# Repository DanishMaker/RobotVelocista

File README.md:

# RobotVelocista
Un robot que corre ya esta joder

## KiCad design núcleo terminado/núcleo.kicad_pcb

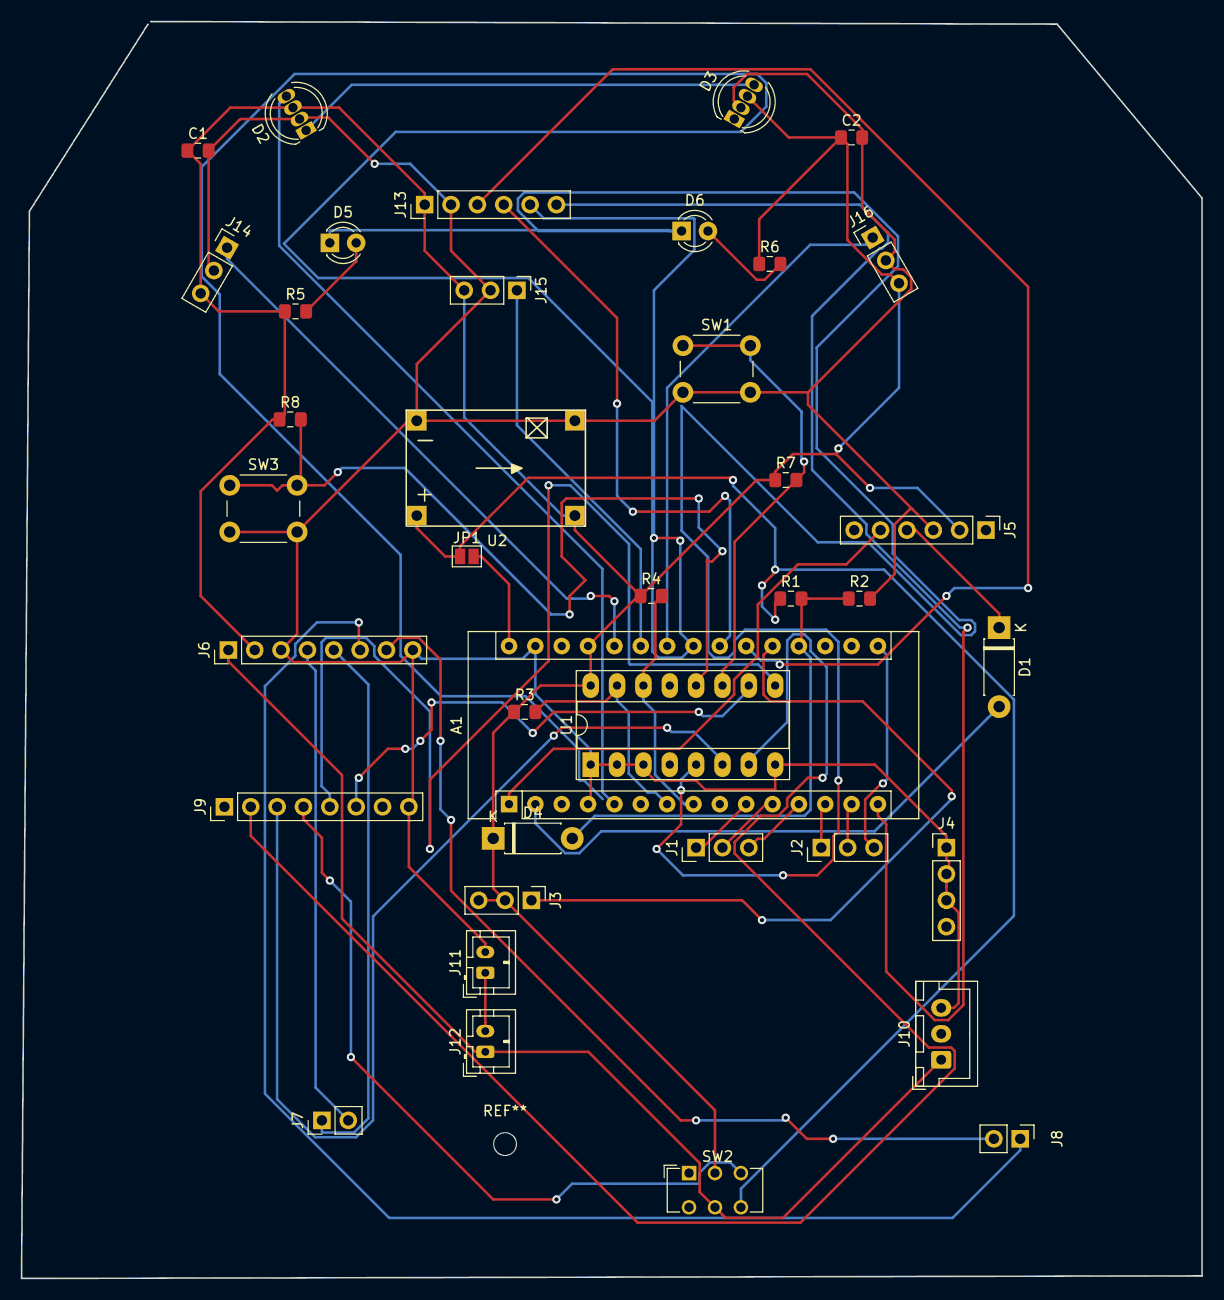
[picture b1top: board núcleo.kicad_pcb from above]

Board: 2 copper layers, 113.8 x 121.2 mm, 39 parts (0 on the bottom side), 42 nets.

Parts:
A1: Arduino_Nano_v3.x; Arduino_Nano
C1, C2: 100nF; C_0805_2012Metric_Pad1.15x1.40mm_HandSolder
D1, D4: D; D_DO-41_SOD81_P7.62mm_Horizontal
D2, D3: NeoPixel_THT; LED_D5.0mm-4_RGB
D5: LED_rojo; LED_D3.0mm
D6: LED_verde; LED_D3.0mm
J1: AUX1; PinHeader_1x03_P2.54mm_Vertical
J2: AUX2; PinHeader_1x03_P2.54mm_Vertical
J3: AUX3; PinHeader_1x03_P2.54mm_Vertical
J4: AUX4; PinHeader_1x04_P2.54mm_Vertical
J5: Conn_01x06; PinHeader_1x06_P2.54mm_Vertical
J6, J9: Conn_01x08; PinHeader_1x08_P2.54mm_Vertical
J7: MOT_IZQ; PinHeader_1x02_P2.54mm_Vertical
J8: MOT_DER; PinHeader_1x02_P2.54mm_Vertical
J10: Conn_01x03; JST_XH_B03B-XH-A_1x03_P2.50mm_Vertical
J11, J12: Conn_01x02; JST_PH_B2B-PH-K_1x02_P2.00mm_Vertical
J13: Sensores_linea; PinHeader_1x06_P2.54mm_Vertical
J14: DIST_IZQ; PinHeader_1x03_P2.54mm_Vertical
J15: DIST_FRONT; PinHeader_1x03_P2.54mm_Vertical
J16: DIST_DCHA; PinHeader_1x03_P2.54mm_Vertical
JP1: Jumper_NO_Small; SolderJumper-2_P1.3mm_Open_Pad1.0x1.5mm
R1: 82k; R_0805_2012Metric_Pad1.15x1.40mm_HandSolder
R2: 120k; R_0805_2012Metric_Pad1.15x1.40mm_HandSolder
R3, R4, R5, R6: R; R_0805_2012Metric_Pad1.15x1.40mm_HandSolder
R7, R8: 10k; R_0805_2012Metric_Pad1.15x1.40mm_HandSolder
SW1, SW3: SW_Push; SW_PUSH_6mm
SW2: SW_DPDT_x2; SW_CuK_JS202011CQN_DPDT_Straight
U1: PCF8574; DIP-16_W7.62mm_Socket_LongPads
U2: DC-DC_BuckModule; DC-DC-MP2307

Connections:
+5V: A1.27, C1.1, C2.1, D2.3, D3.3, D4.1, J3.2, J3.3, J5.2, J6.2, J13.1, J14.3, J15.3, J16.3, R3.1, R4.1, R5.1, R6.1, R7.1, R8.1, SW2.2, U1.16, U2.3
A1: A1.20, J3.1
B1: R7.2, SW1.1, U1.11
B2: R8.2, SW3.1, U1.12
BAT: A1.19, D4.2, R1.2, R2.1
BT_RX: A1.1, J5.5
BT_TX: A1.2, D1.2
D7: A1.10, J1.1
D8: A1.11, J1.2
D9: A1.12, J1.3
D10: A1.13, J2.1
D11: A1.14, J2.2
D13: A1.16, J2.3
DIR_DER_1: J9.5, U1.9
DIR_DER_2: J9.6, U1.10
DIR_IZQ_1: J9.3, U1.6
DIR_IZQ_2: J9.2, U1.7
DIST_DCHA: A1.24, J16.1
DIST_FRONT: A1.25, J15.1
DIST_IZQ: A1.26, J14.1
GND: A1.4, A1.29, C1.2, C2.2, D2.2, D3.2, J4.1, J4.2, J4.3, J5.3, J6.3, J6.8, J9.8, J10.3, J11.2, J13.2, J14.2, J15.2, J16.2, R2.2, SW1.2, SW3.2, U1.1, U1.2, U1.3, U1.8, U2.2, U2.4
I2C_SCL: A1.8, R4.2, U1.14
I2C_SDA: A1.7, R3.2, U1.15
LED_R: D5.1, D6.1, U1.5
LINEA_1: A1.21, J13.3
LINEA_2: A1.22, J13.4
LINEA_3: A1.23, J13.5
LINEA_SEL: A1.15, J13.6
M_DER_+: J6.7, J8.2
M_DER_-: J6.6, J8.1
M_IZQ_+: J6.4, J7.2
M_IZQ_-: J6.5, J7.1
NEO: A1.5, D2.4
unnamed: D1.1, J5.4
unnamed: D2.1, D3.4
unnamed: D5.2, R5.2
unnamed: D6.2, R6.2
unnamed: J11.1, J12.2
STBY_MOT: J9.4, SW2.3
VBAT: J6.1, J10.1, J12.1, SW2.5
VCC: A1.30, JP1.2
VDD: JP1.1, R1.1, SW2.6, U2.1

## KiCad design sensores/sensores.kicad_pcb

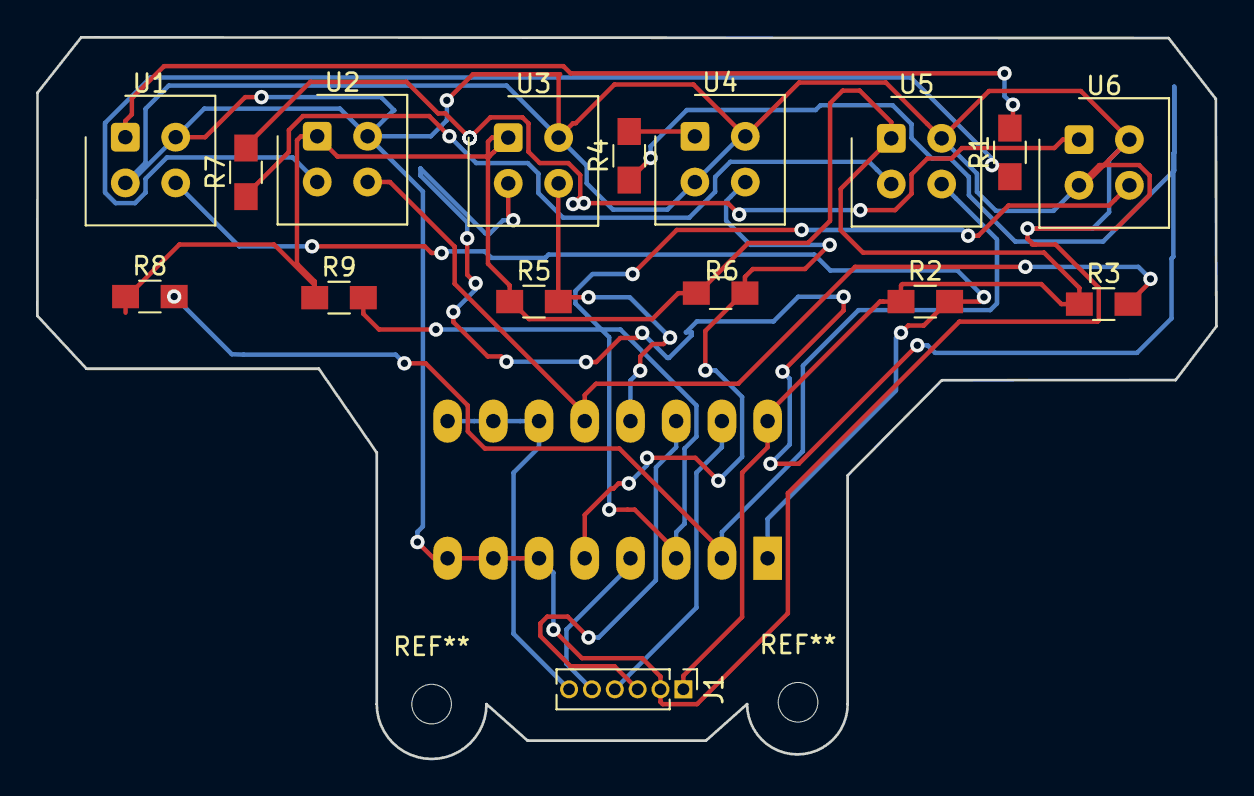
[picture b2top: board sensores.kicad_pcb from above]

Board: 2 copper layers, 65.5 x 40.1 mm, 17 parts (1 on the bottom side), 18 nets.

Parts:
J1: Conn_01x06_Female; Pin_Header_Straight_1x06_Pitch1.27mm
R1, R4, R7: 82; R_0805_HandSoldering
R2, R3, R5, R6, R8, R9: 10k; R_0805_HandSoldering
U1, U2, U3, U4, U5, U6: CNY70; Vishay_CNY70
U7: 4053; DIP-16_W7.62mm_LongPads

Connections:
+5V: J1.1, R2.1, R3.1, R5.1, R6.1, R8.1, R9.1, U2.1, U3.1, U5.1, U7.16
/linea1: J1.3, U7.14
/linea2: J1.4, U7.15
/linea3: J1.5, U7.4
/linea_selec: J1.6, U7.9, U7.10, U7.11
/sensor1: R3.2, U2.3, U7.12
/sensor2: R5.2, U3.3, U7.13
/sensor3: R8.2, U5.3, U7.2
/sensor4: R2.2, U1.3, U7.1
/sensor5: R6.2, U4.3, U7.5
/sensor6: R9.2, U6.3, U7.3
GND: J1.2, U1.2, U1.4, U2.4, U3.4, U4.2, U4.4, U5.4, U6.2, U6.4, U7.6, U7.7, U7.8
unnamed: R1.1, U2.2
unnamed: R1.2, U1.1
unnamed: R4.1, U3.2
unnamed: R4.2, U4.1
unnamed: R7.1, U5.2
unnamed: R7.2, U6.1

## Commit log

2018-11-17 placa empezada
2018-11-24 Add files via upload
    Placa frontal terminada
2018-12-01 Núcleo
    He creado el esquema de la parte central del robot
2018-12-15 Nucleo empezado
    Empezando a enrutar las huellas de los componentes
2019-01-12 finalisado
